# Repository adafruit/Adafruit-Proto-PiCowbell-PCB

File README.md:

## Adafruit PiCowbell Proto for Pico PCB

<a href="http://www.adafruit.com/products/5200"><br/>
Click here to purchase one from the Adafruit shop</a>

PCB files for the Adafruit PiCowbell Proto for Pico. 

Format is EagleCAD schematic and board layout
* https://www.adafruit.com/product/5200

### Description

Ding dong! Hear that? It's the PiCowbell ringing, letting you know that the new Adafruit PiCowbell Proto is finally in stock and ready to assist your Raspberry Pi Pico and Pico W project with handy hardware and practical prototyping.

The PiCowbell Proto is the same size and shape as a Pico, and is intended to socket underneath to make programming and sensor connectivity easy. Reset button? Yes! STEMMA QT / Qwiic connector for fast I2C? Indeed. 

The PiCowbell Proto provides you with:
* Right angle reset button that sticks out the end
* Right angle JST SH connector for I2C / Stemma QT / Qwiic connection. Or can use it for plain GPIO wiring if you don't have any I2C devices to attach. Provides 3V, GND, IO4 (SDA), and IO5 (SCL)
* Extra set of 4 breakout holes next to the JST SH in case you want more I2C connection or want to re-assign the I2C port.
* 13 rows of 4-hole connected strips in the center area. You can cut the traces between the holes but they're intended to be treated like a mini-mini breadboard
* Every pad on the Pico has a duplicate hole pad next to it for solder-jumpering
* The ground pads have white silkscreen rectangles to easily identify, plus one long ground strip near the reset button
* One long strip of connected holes for 3.3V power
* Gold plated pads for easy soldering

### License

Adafruit invests time and resources providing this open source design, please support Adafruit and open-source hardware by purchasing products from [Adafruit](https://www.adafruit.com)!

Designed by Limor Fried/Ladyada for Adafruit Industries.

Creative Commons Attribution/Share-Alike, all text above must be included in any redistribution. 
See license.txt for additional details.

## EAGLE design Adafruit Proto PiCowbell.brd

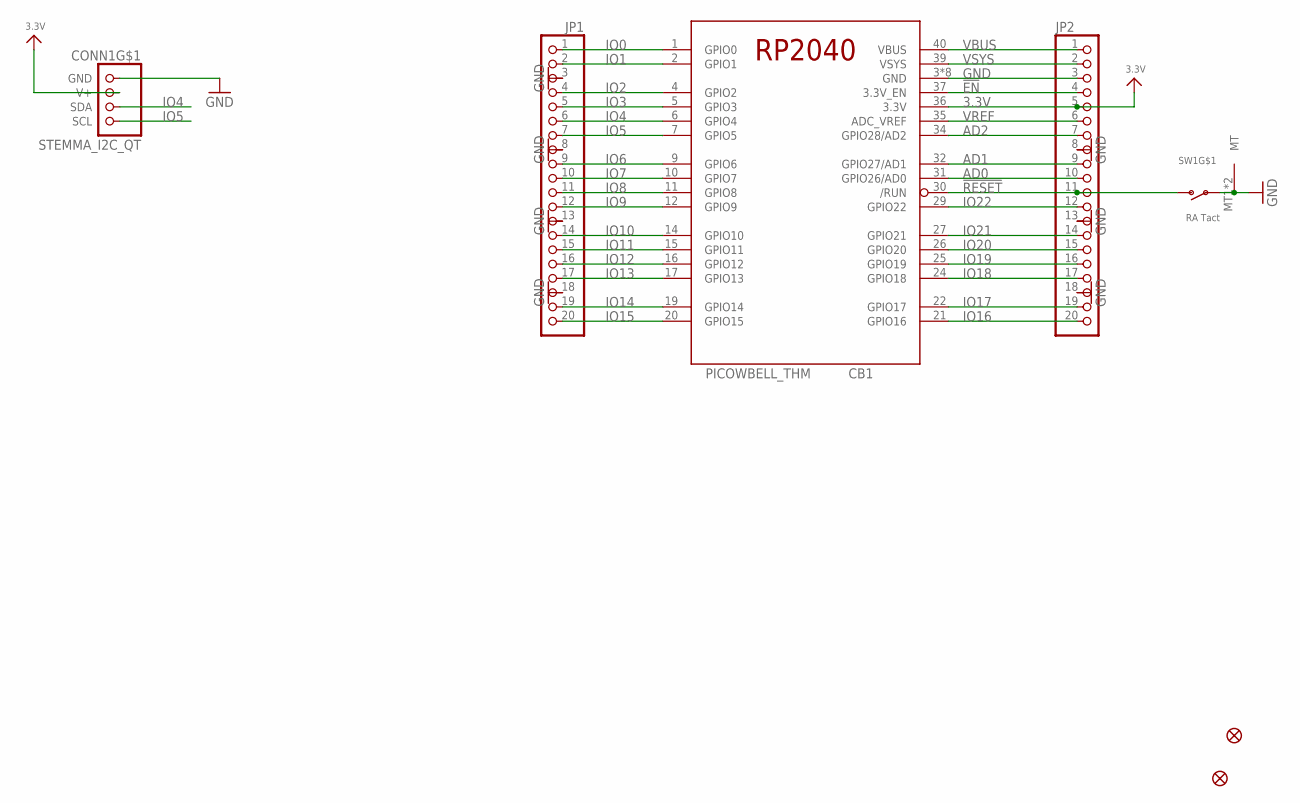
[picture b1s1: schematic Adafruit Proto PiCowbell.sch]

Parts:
CB1: PICOWBELL_THM; PICOWBELL
CONN1: STEMMA_I2C_QT; JST_SH4
FID1, FID2: FIDUCIAL_1MM
JP1, JP2: HEADER-1X20_70MIL; 1X20_ROUND_70MIL
SW1: RA Tact; SPST_TACTILE_RA

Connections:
3.3V: CB1.36 (3.3V), CONN1.2 (V+), JP2.5
!EN: CB1.37 (3.3V_EN), JP2.4
!RESET: CB1.30 (/RUN), JP2.11, SW1.2 (S)
AD0: CB1.31 (GPIO26/AD0), JP2.10
AD1: CB1.32 (GPIO27/AD1), JP2.9
AD2: CB1.34 (GPIO28/AD2), JP2.7
GND: CB1.3 (GND), CB1.8 (GND), CB1.13 (GND), CB1.18 (GND), CB1.23 (GND), CB1.28 (GND), CB1.33 (GND), CB1.38 (GND), CONN1.1 (GND), JP1.3, JP1.8, JP1.13, JP1.18, JP2.3, JP2.8, JP2.13, JP2.18, SW1.1, SW1.MT1 (MT), SW1.MT2 (MT)
IO0: CB1.1 (GPIO0), JP1.1
IO1: CB1.2 (GPIO1), JP1.2
IO2: CB1.4 (GPIO2), JP1.4
IO3: CB1.5 (GPIO3), JP1.5
IO4: CB1.6 (GPIO4), CONN1.3 (SDA), JP1.6
IO5: CB1.7 (GPIO5), CONN1.4 (SCL), JP1.7
IO6: CB1.9 (GPIO6), JP1.9
IO7: CB1.10 (GPIO7), JP1.10
IO8: CB1.11 (GPIO8), JP1.11
IO9: CB1.12 (GPIO9), JP1.12
IO10: CB1.14 (GPIO10), JP1.14
IO11: CB1.15 (GPIO11), JP1.15
IO12: CB1.16 (GPIO12), JP1.16
IO13: CB1.17 (GPIO13), JP1.17
IO14: CB1.19 (GPIO14), JP1.19
IO15: CB1.20 (GPIO15), JP1.20
IO16: CB1.21 (GPIO16), JP2.20
IO17: CB1.22 (GPIO17), JP2.19
IO18: CB1.24 (GPIO18), JP2.17
IO19: CB1.25 (GPIO19), JP2.16
IO20: CB1.26 (GPIO20), JP2.15
IO21: CB1.27 (GPIO21), JP2.14
IO22: CB1.29 (GPIO22), JP2.12
VBUS: CB1.40 (VBUS), JP2.1
VREF: CB1.35 (ADC_VREF), JP2.6
VSYS: CB1.39 (VSYS), JP2.2

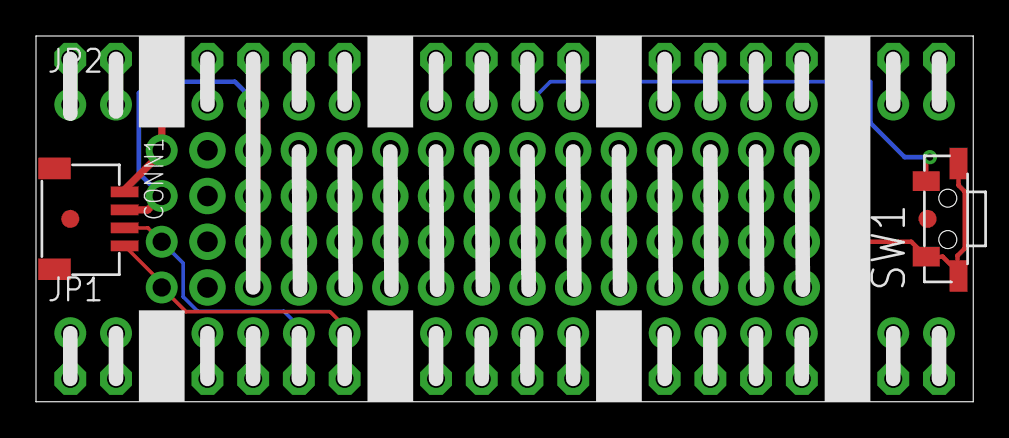
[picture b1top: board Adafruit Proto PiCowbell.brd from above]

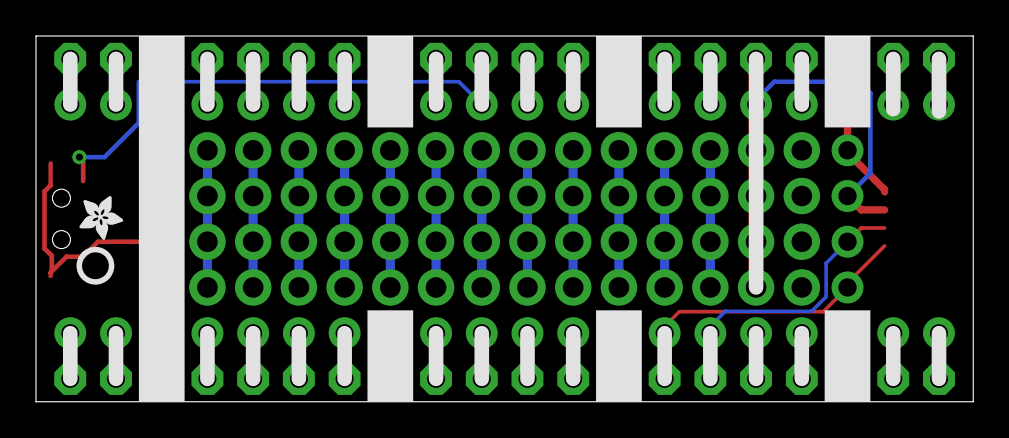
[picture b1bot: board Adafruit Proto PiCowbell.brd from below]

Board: 2 copper layers, 52.1 x 20.3 mm, 77 parts (35 on the bottom side), 33 nets.

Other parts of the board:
PLABEL0: PLABEL0
PLABEL1: PLABEL1
PLABEL2: PLABEL2
PLABEL3: PLABEL3
PLABEL4: PLABEL4
PLABEL5: PLABEL5
PLABEL6: PLABEL6
PLABEL7: PLABEL7
PLABEL8: PLABEL8
PLABEL9: PLABEL9
PLABEL10: PLABEL10
PLABEL11: PLABEL11
PLABEL12: PLABEL12
PLABEL13: PLABEL13
PLABEL14: PLABEL14
PLABEL15: PLABEL15
PLABEL16: PLABEL16
PLABEL17: PLABEL17
PLABEL18: PLABEL18
PLABEL19: PLABEL19
PLABEL20: PLABEL20
PLABEL21: PLABEL21
PLABEL22: PLABEL22
PLABEL23: PLABEL23
PLABEL24: PLABEL24
PLABEL25: PLABEL25
PLABEL26: PLABEL26
PLABEL27: PLABEL27
PLABEL28: PLABEL28
PLABEL29: PLABEL29
PLABEL30: PLABEL30
PLABEL31: PLABEL31
PLABEL32: PLABEL32
PLABEL33: PLABEL33
PLABEL34: PLABEL34
PLABEL35: PLABEL35
PLABEL36: PLABEL36
PLABEL37: PLABEL37
PLABEL38: PLABEL38
PLABEL39: PLABEL39
PLABEL40: PLABEL40
PLABEL41: PLABEL41
PLABEL42: PLABEL42
PLABEL43: PLABEL43
PLABEL44: PLABEL44
PLABEL45: PLABEL45
PLABEL46: PLABEL46
PLABEL47: PLABEL47
PLABEL48: PLABEL48
PLABEL49: PLABEL49
PLABEL50: PLABEL50
PLABEL51: PLABEL51
PLABEL52: PLABEL52
PLABEL53: PLABEL53
PLABEL54: PLABEL54
PLABEL55: PLABEL55
PLABEL56: PLABEL56
PLABEL57: PLABEL57
PLABEL58: PLABEL58
PLABEL59: PLABEL59
PLABEL60: PLABEL60
PLABEL61: PLABEL61
PLABEL62: PLABEL62
PLABEL63: PLABEL63
PLABEL64: PLABEL64
PLABEL65: PLABEL65
PLABEL66: PLABEL66
PLABEL67: PLABEL67
U$2: ADAFRUIT_2.5MM
U$6: PCBFEAT-REV-040

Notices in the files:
parts and their libraries:
microbuilder: This work is placed in the public domain, and may be freely used for commercial and non-commercial work with the following conditions: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
